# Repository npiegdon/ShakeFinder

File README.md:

# ShakeFinder
## A low-cost, high-sensitivity vibration sensor

**Watch the [design video](https://www.youtube.com/watch?v=hmemnF16wfw) on YouTube!**

ShakeFinder is based on [David Houlding's](https://davidhoulding.blogspot.com/2014/02/high-sensitivity-vibration-sensor-using.html) vibration sensor with a number of improvements.  The most notable is an open-drain output so it can be connected to non-5V microcontrollers (like Raspberry Pi) easily.

This sensor was created for use with my homemade 8mm film scanner, the [ReelSlow8](https://forums.kinograph.cc/t/the-reelslow8-film-scanner/2491).

Sample code is provided for Arduino Uno.

## Bill of Materials

| Part                               | Value                                        | Package/Notes                                               | Link                                                                                                    |
| ---------------------------------- | -------------------------------------------- | ----------------------------------------------------------- | ------------------------------------------------------------------------------------------------------- |
| Calibration weight                 | 200g                                         | lowest-grade                                                | [Amazon](https://www.amazon.com/dp/B0BLNHJLXJ)                                                          |
| Piezo element                      | 35mm disc                                    | generic                                                     | [Amazon](https://www.amazon.com/dp/B084KHH7B6)                                                          |
| 2x1 PicoBlade connector (optional) | for the piezo element                        | Molex WM1720-ND for connector, 900-0500588020CT-ND for pins |                                                                                                         |
| 2x1 PicoBlade socket (optional)    | for the PCB                                  | Molex WM1742-ND                                             |                                                                                                         |
| 2.5mm TRS jack                     | through-hole, right angle                    | SJ1-2503A                                                   | [DigiKey](https://www.digikey.com/en/products/detail/cui-devices/SJ1-2503A/738680)                      |
| Double-diode                       | ~0.5V drop at no current                     | BAV99, SOT-23                                               | [DigiKey](https://www.digikey.com/en/products/detail/nexperia-usa-inc/BAV99-235/1232158)                |
| front end op-amp                   | Single supply, rail-to-rail, Vss-1 / Vdd+1   | MCP6001T, SOT-23-5                                          | [DigiKey](https://www.digikey.com/en/products/detail/microchip-technology/MCP6001T-I-OT/551760)         |
| Potentiometer                      | Upright, TH, 100k, Log                       | PTV09A-4015U-A104                                           | [DigiKey](https://www.digikey.com/en/products/detail/bourns-inc/PTV09A-4015U-A104/6153483)              |
| Retriggerable Monostable           | SM8 is $0.10 more, but easier to hand-solder | SN74LVC1G123DCTR, 8SSOP (SM8)                               | [DigiKey](https://www.digikey.com/en/products/detail/texas-instruments/SN74LVC1G123DCTR/863597)         |
| Output N-ch FET                    | This one has nice characteristics            | AOSS32136C                                                  | [DigiKey](https://www.digikey.com/en/products/detail/alpha-omega-semiconductor-inc/AOSS32136C/11567433) |
| C1                                 | 10n                                          | 0603 jellybean                                              |                                                                                                         |
| C2                                 | 1u                                           | 0603 jellybean                                              |                                                                                                         |
| C3                                 | 10u                                          | 1206 jellybean                                              |                                                                                                         |
| C5, C4                             | 100n                                         | 0603 jellybean                                              |                                                                                                         |
| D2                                 | red (or whatever)                            | 5mm through-hole jellybean                                  |                                                                                                         |
| R1, R9                             | 100k                                         | 0805 jellybean                                              |                                                                                                         |
| R2, R4, R5                         | 10k                                          | 0805 jellybean                                              |                                                                                                         |
| R7, R8                             | 1k                                           | 0805 jellybean                                              |                                                                                                         |
| R6                                 | Anywhere from 10k to 100k*                   | 0805 jellybean                                              |                                                                                                         |

\* The schematic lists 10k for R6.  The YouTube video demonstrates R6 at 33k.  The value of this resistor controls the length of the pulse.  Using 100k for R6 would cause even less chatter on the output.  Choose whatever you like here.  50k might be a reasonable place to start.

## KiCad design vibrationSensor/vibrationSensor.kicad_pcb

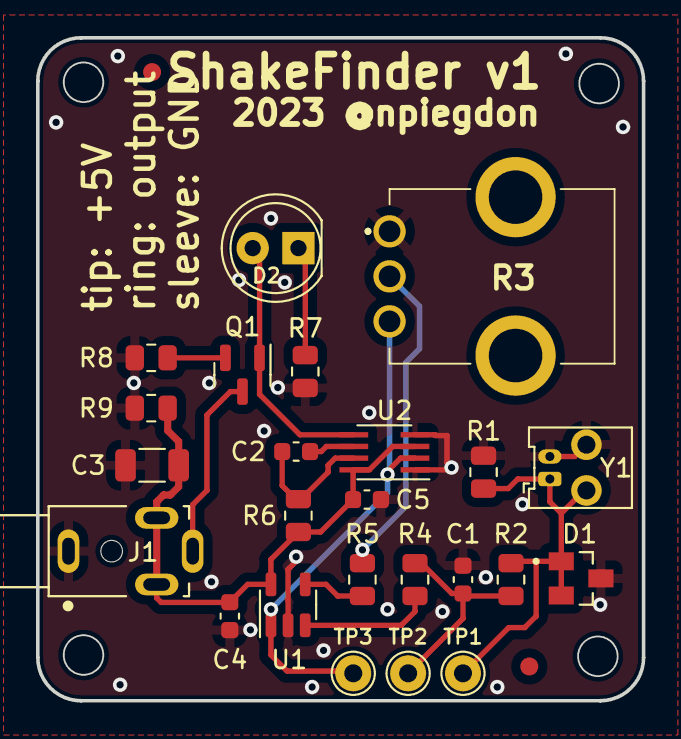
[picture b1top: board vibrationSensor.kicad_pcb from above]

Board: 2 copper layers, 33.7 x 36.8 mm, 27 parts (0 on the bottom side), 14 nets.

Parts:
C1: 10n; C_0603_1608Metric
C2: 1u; C_0603_1608Metric
C3: 10u; C_1206_3216Metric
C4, C5: 100n; C_0603_1608Metric
D1: BAV99; DIO_BAV99
D2: RED; LED_D5.0mm_IRGrey
FID1, FID2: Fiducial; Fiducial_1mm_Mask2mm
J1: 2.5mm TRS; CUI_SJ1-2503A
J2: Conn_01x02_Pin; PinHeader_1x02_P2.54mm_Vertical
Q1: AOSS32136C; SOT-23
R1, R9: 100k; R_0805_2012Metric
R2, R4, R5, R6: 10k; R_0805_2012Metric
R3: 100k; Bournes PTV09A4020UB104
R7, R8: 1K; R_0805_2012Metric
TP1: Crystal; TestPoint_THTPad_D2.0mm_Drill1.0mm
TP2: LPF; TestPoint_THTPad_D2.0mm_Drill1.0mm
TP3: amp; TestPoint_THTPad_D2.0mm_Drill1.0mm
U1: MCP6001; SOT-23-5
U2: 74LVC1G123; SSOP-8_2.95x2.8mm_P0.65mm
Y1: Piezo; Molex_PicoBlade_53048-0210_1x02_P1.25mm_Horizontal

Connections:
+5V: C3.1, C4.1, C5.1, J1.2, J1.3, R6.1, R9.1, U1.5 (V+), U2.3 (~CLR), U2.8 (VCC)
GND: C1.2, C3.2, C4.2, C5.2, D1.3, J1.1, J2.2, R1.2, R3.1, R7.2, R8.2, R9.2, U1.2 (V-), U2.1 (~A), U2.4 (GND), Y1.2
unnamed: C1.1, R2.2, R4.1, TP2.1
unnamed: D2.2 (A), Q1.1 (G), U2.5 (Q)
unnamed: D2.1 (K), R7.1
unnamed: D1.1, D1.2, J2.1, R1.1, R2.1, TP1.1, Y1.1
unnamed: Q1.2 (S), R8.1
unnamed: R3.2, R5.1
unnamed: R4.2, U1.3 (+)
unnamed: R5.2, U1.4 (-)
unnamed: R3.3, TP3.1, U1.1, U2.2 (B)
unnamed: C2.2, U2.6 (Cext)
unnamed: C2.1, R6.2, U2.7 (RCext)
out: J1.4, Q1.3 (D)

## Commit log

2024-05-03 Initial add
2024-05-03 Make it look nicer.
2024-05-03 Maybe a cache thing?
    Let's rename it.
2024-05-04 Link to the YouTube video.
